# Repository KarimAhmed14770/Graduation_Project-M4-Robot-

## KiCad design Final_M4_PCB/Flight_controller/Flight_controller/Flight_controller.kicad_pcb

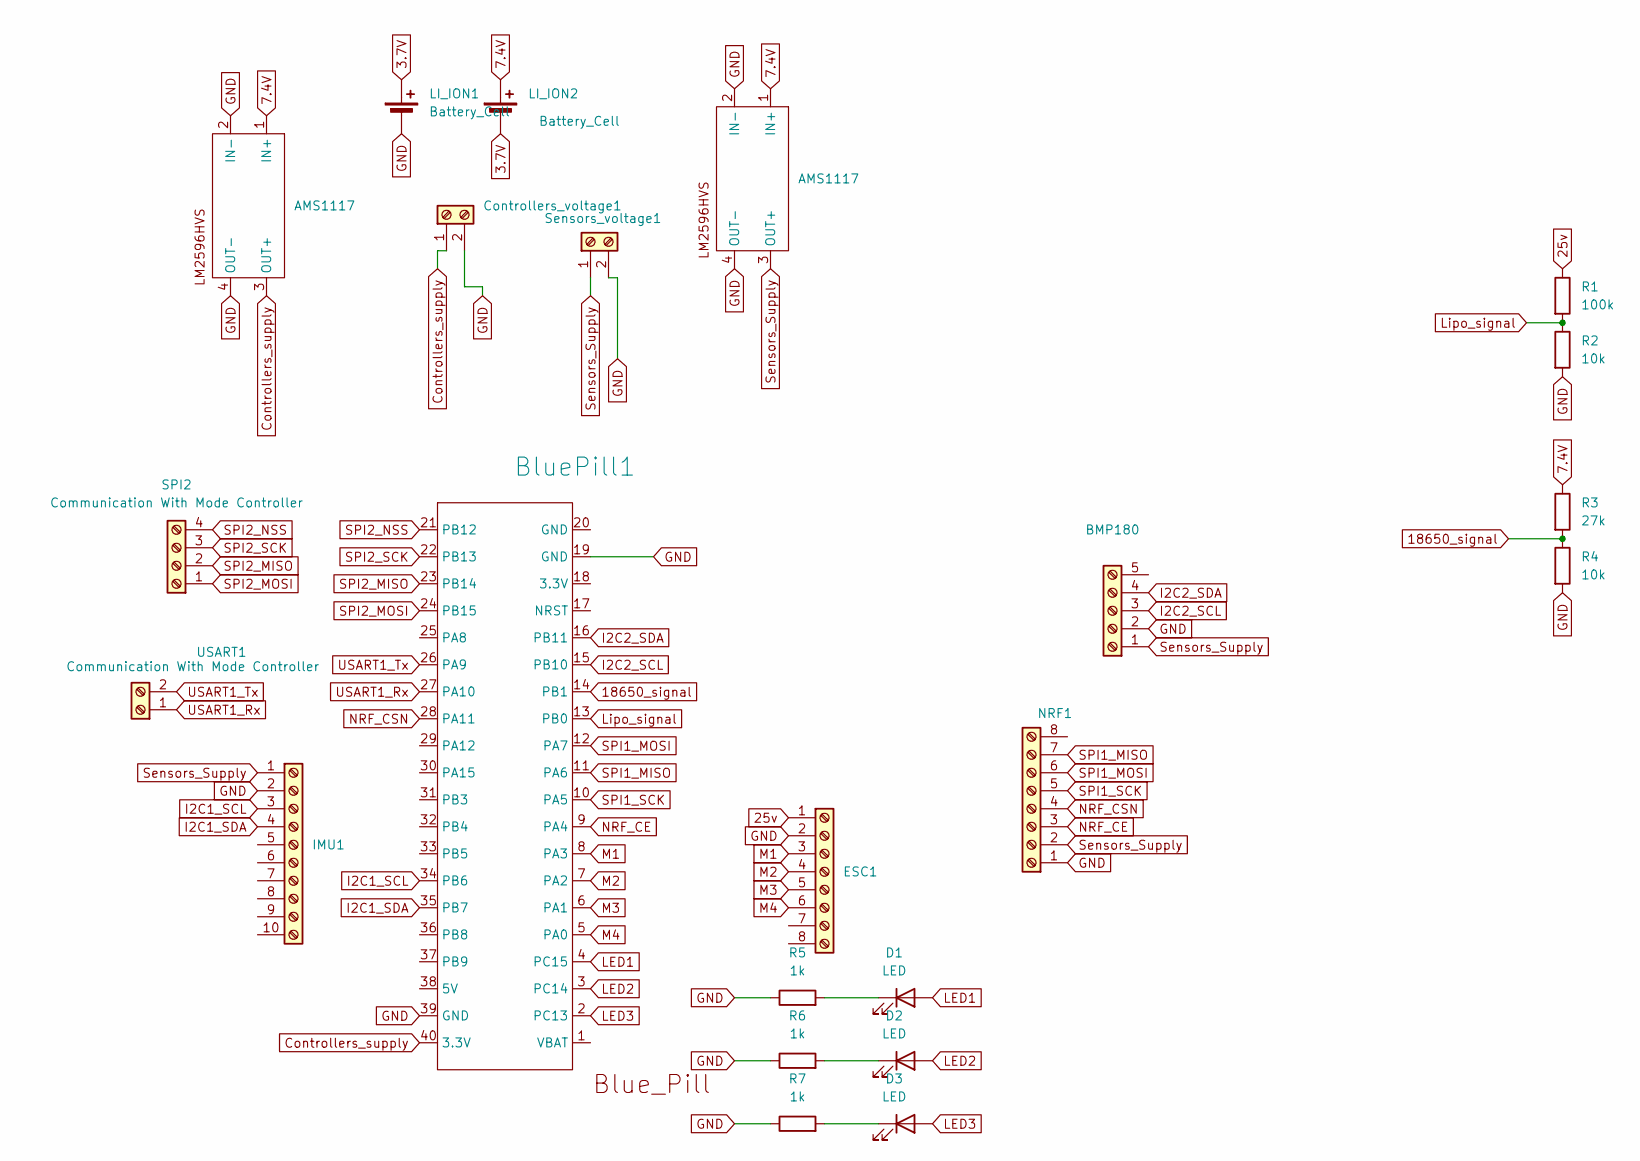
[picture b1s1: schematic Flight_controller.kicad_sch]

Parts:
AMS1117: 3.3v_regulator
BMP180: Screw_Terminal_01x05; BMP180
BluePill1: blue_pill
Controllers_voltage1: Screw_Terminal_01x02; PinHeader_1x02_P2.54mm_Vertical
D1, D2, D3: LED; LED_D3.0mm
ESC1: Screw_Terminal_01x08; ESC
IMU1: Screw_Terminal_01x10; MPU9250
LI_ION1, LI_ION2: Battery_Cell; PinHeader_1x02_P2.54mm_Vertical
NRF1: Screw_Terminal_01x08; NRF24L1
R1: 100k; R_Axial_DIN0204_L3.6mm_D1.6mm_P2.54mm_Vertical
R2, R4: 10k; R_Axial_DIN0204_L3.6mm_D1.6mm_P2.54mm_Vertical
R3: 27k; R_Axial_DIN0204_L3.6mm_D1.6mm_P2.54mm_Vertical
R5, R6, R7: 1k; R_Axial_DIN0204_L3.6mm_D1.6mm_P2.54mm_Vertical
SPI2: Communication With Mode Controller; PinHeader_1x04_P2.54mm_Vertical
Sensors_voltage1: Screw_Terminal_01x02; PinHeader_1x02_P2.54mm_Vertical
USART1: Communication With Mode Controller; PinHeader_1x02_P2.54mm_Vertical

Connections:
3.7V: LI_ION1.1 (+), LI_ION2.2 (-)
7.4V: AMS1117.1 (IN+), LI_ION2.1 (+), R3.1; also elsewhere on the board
25v: ESC1.1, R1.1
18650_signal: BluePill1.14 (PB1), R3.2, R4.1
Controllers_supply: AMS1117.3 (OUT+), BluePill1.40 (3.3V), Controllers_voltage1.1; also elsewhere on the board
GND: AMS1117.2 (IN-), AMS1117.4 (OUT-), BMP180.2, BluePill1.19 (GND), BluePill1.39 (GND), Controllers_voltage1.2, ESC1.2, IMU1.2, LI_ION1.2 (-), NRF1.1, R2.2, R4.2, R5.1, R6.1, R7.1, Sensors_voltage1.2; also elsewhere on the board
I2C1_SCL: BluePill1.34 (PB6), IMU1.3
I2C1_SDA: BluePill1.35 (PB7), IMU1.4
I2C2_SCL: BMP180.3, BluePill1.15 (PB10)
I2C2_SDA: BMP180.4, BluePill1.16 (PB11)
LED1: BluePill1.4 (PC15), D1.2 (A)
LED2: BluePill1.3 (PC14), D2.2 (A)
LED3: BluePill1.2 (PC13), D3.2 (A)
Lipo_signal: BluePill1.13 (PB0), R1.2, R2.1
M1: BluePill1.8 (PA3), ESC1.3
M2: BluePill1.7 (PA2), ESC1.4
M3: BluePill1.6 (PA1), ESC1.5
M4: BluePill1.5 (PA0), ESC1.6
NRF_CE: BluePill1.9 (PA4), NRF1.3
NRF_CSN: BluePill1.28 (PA11), NRF1.4
unnamed: D1.1 (K), R5.2
unnamed: D2.1 (K), R6.2
unnamed: D3.1 (K), R7.2
SPI1_MISO: BluePill1.11 (PA6), NRF1.7
SPI1_MOSI: BluePill1.12 (PA7), NRF1.6
SPI1_SCK: BluePill1.10 (PA5), NRF1.5
SPI2_MISO: BluePill1.23 (PB14), SPI2.2
SPI2_MOSI: BluePill1.24 (PB15), SPI2.1
SPI2_NSS: BluePill1.21 (PB12), SPI2.4
SPI2_SCK: BluePill1.22 (PB13), SPI2.3
Sensors_Supply: AMS1117.3 (OUT+), BMP180.1, IMU1.1, NRF1.2, Sensors_voltage1.1; also elsewhere on the board
USART1_Rx: BluePill1.27 (PA10), USART1.1
USART1_Tx: BluePill1.26 (PA9), USART1.2

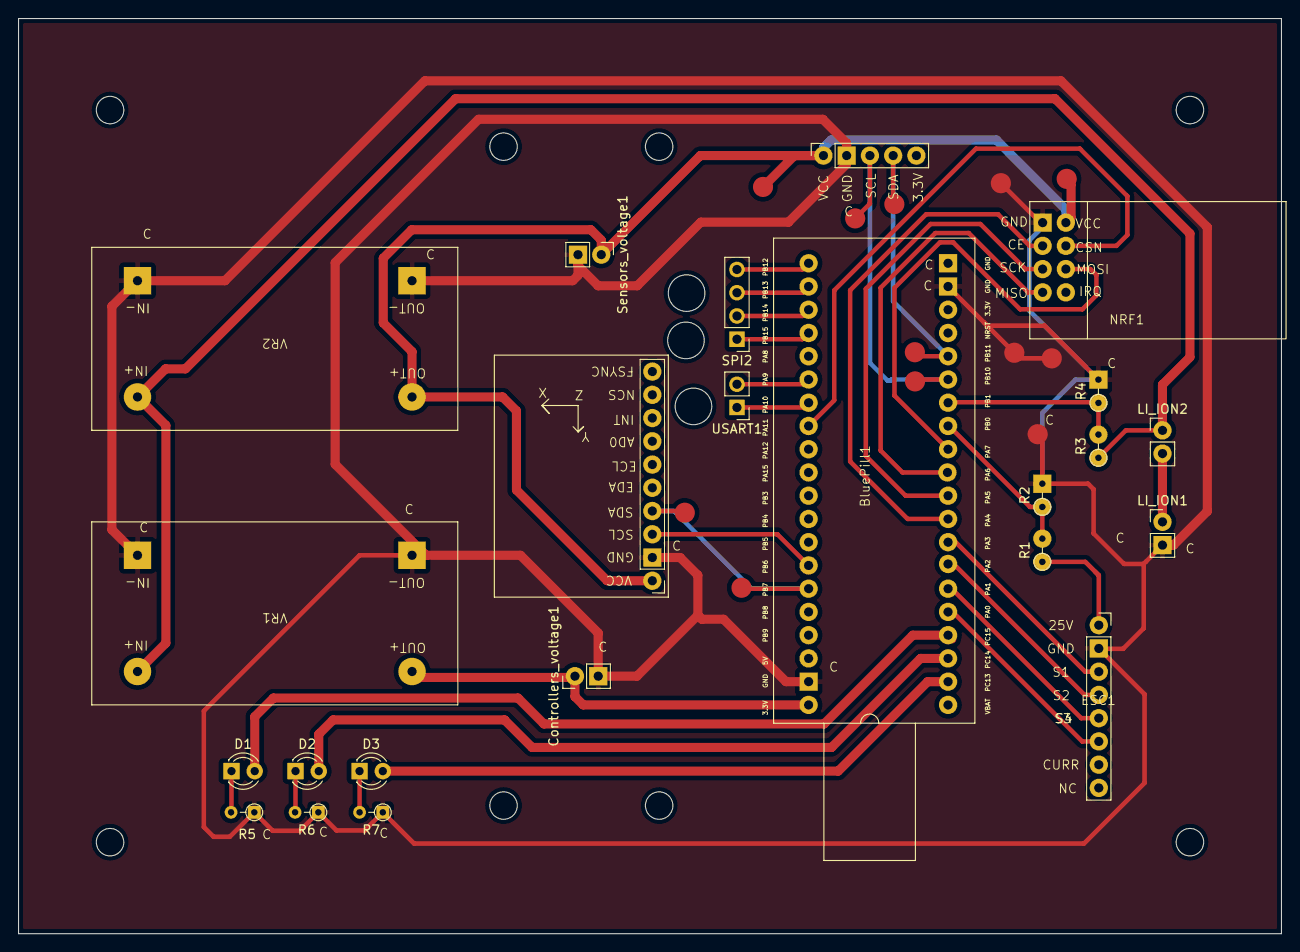
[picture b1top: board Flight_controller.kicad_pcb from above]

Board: 2 copper layers, 138.0 x 100.0 mm, 23 parts (0 on the bottom side), 33 nets.

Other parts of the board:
VR1, VR2: 3.3v_regulator

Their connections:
7.4V: VR1.1 (IN+), VR2.1 (IN+); also elsewhere on the board
Controllers_supply: VR1.3 (OUT+); also elsewhere on the board
GND: VR1.2 (IN-), VR1.4 (OUT-), VR2.2 (IN-), VR2.4 (OUT-); also elsewhere on the board
Sensors_Supply: VR2.3 (OUT+); also elsewhere on the board

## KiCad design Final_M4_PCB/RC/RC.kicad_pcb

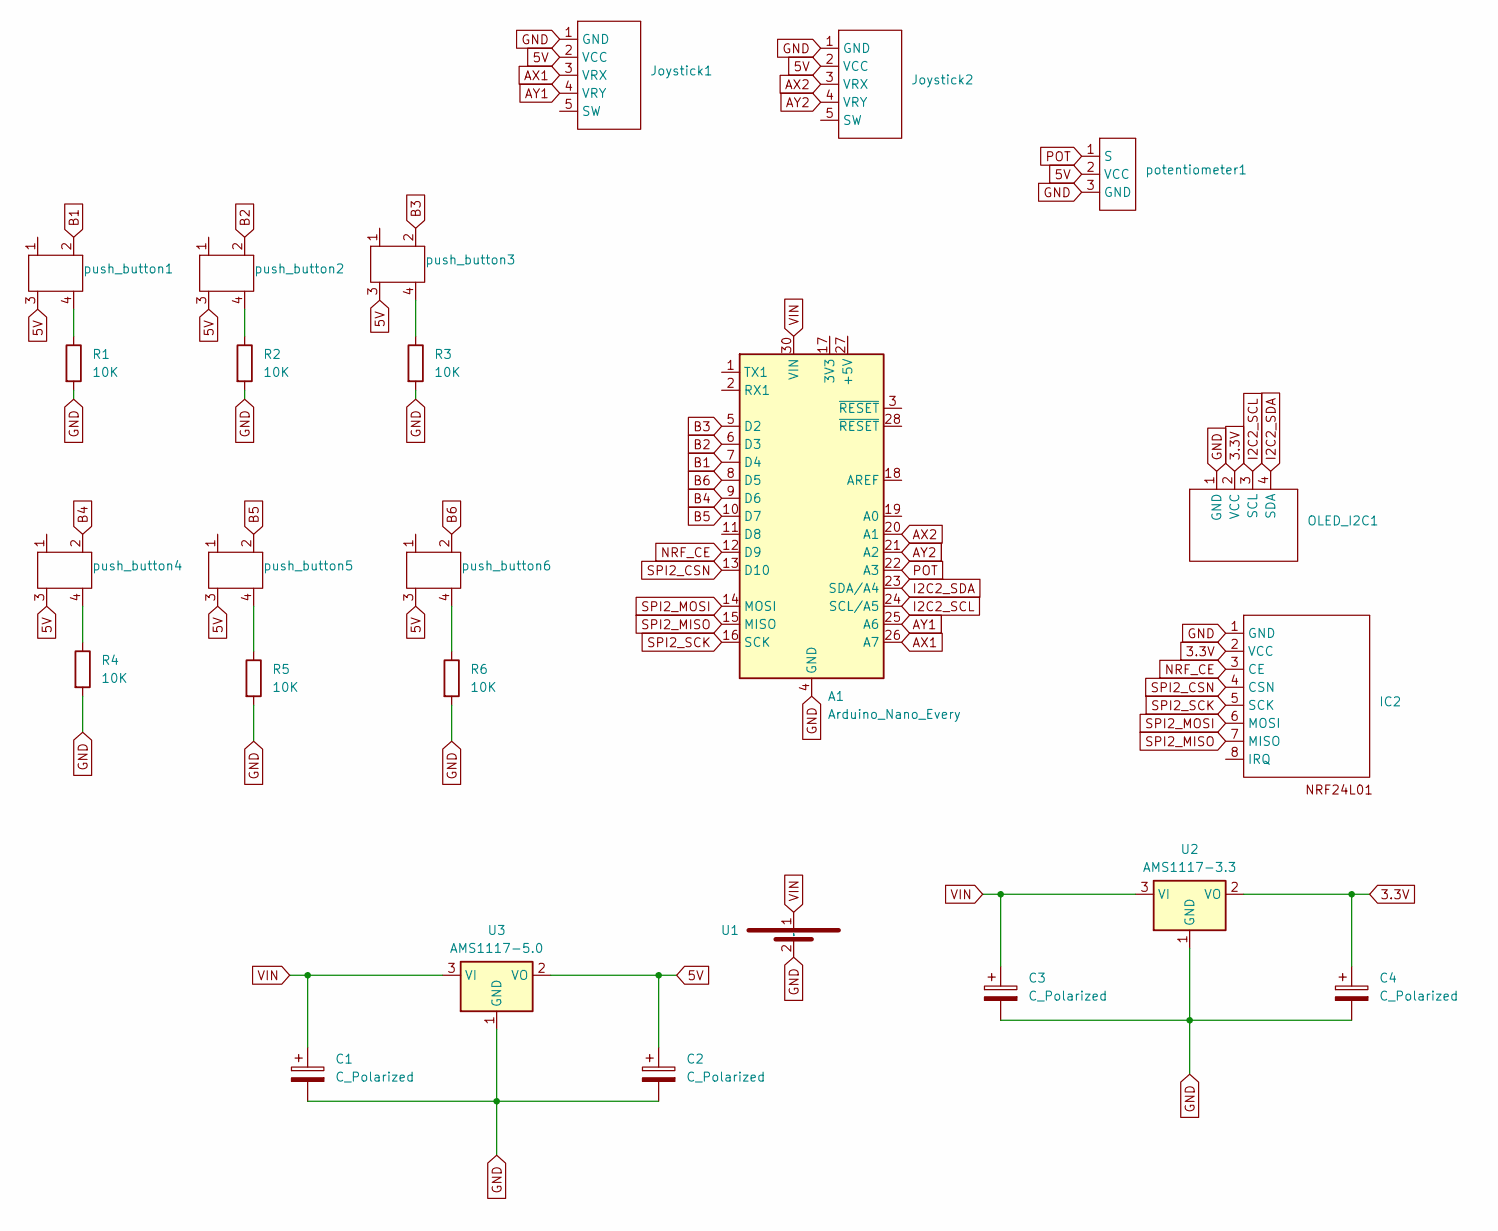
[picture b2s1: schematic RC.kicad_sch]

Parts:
A1: Arduino_Nano_Every; Arduino_Nano
C1, C2, C3, C4: C_Polarized; two_pin_headers2.54
IC2: NRF_ANTENNA
Joystick1, Joystick2: Joystick
OLED_I2C1: OLED
R1, R2, R3, R4, R5, R6: 10K; R_Axial_DIN0204_L3.6mm_D1.6mm_P5.08mm_Horizontal
U1: TerminalBlock_bornier-2_P5.08mm
U2: AMS1117-3.3; SOT-223-3_TabPin2
U3: AMS1117-5.0; SOT-223-3_TabPin2
potentiometer1: POT
push_button1, push_button2, push_button3, push_button4, push_button5, push_button6: Push_Button

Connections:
3.3V: C4.1, IC2.2 (VCC), OLED_I2C1.2 (VCC), U2.2 (VO)
5V: C2.1, Joystick1.2 (VCC), Joystick2.2 (VCC), U3.2 (VO), potentiometer1.2 (VCC), push_button1.3, push_button2.3, push_button3.3, push_button4.3, push_button5.3, push_button6.3
AX1: A1.26 (A7), Joystick1.3 (VRX)
AX2: A1.20 (A1), Joystick2.3 (VRX)
AY1: A1.25 (A6), Joystick1.4 (VRY)
AY2: A1.21 (A2), Joystick2.4 (VRY)
B1: A1.7 (D4), push_button1.2
B2: A1.6 (D3), push_button2.2
B3: A1.5 (D2), push_button3.2
B4: A1.9 (D6), push_button4.2
B5: A1.10 (D7), push_button5.2
B6: A1.8 (D5), push_button6.2
GND: A1.4 (GND), A1.29 (GND), C1.2, C2.2, C3.2, C4.2, IC2.1 (GND), Joystick1.1 (GND), Joystick2.1 (GND), OLED_I2C1.1 (GND), R1.2, R2.2, R3.2, R4.2, R5.2, R6.2, U1.2 (GND), U2.1 (GND), U3.1 (GND), potentiometer1.3 (GND)
I2C2_SCL: A1.24 (SCL/A5), OLED_I2C1.3 (SCL)
I2C2_SDA: A1.23 (SDA/A4), OLED_I2C1.4 (SDA)
NRF_CE: A1.12 (D9), IC2.3 (CE)
unnamed: R1.1, push_button1.4
unnamed: R2.1, push_button2.4
unnamed: R3.1, push_button3.4
unnamed: R4.1, push_button4.4
unnamed: R5.1, push_button5.4
unnamed: R6.1, push_button6.4
POT: A1.22 (A3), potentiometer1.1 (S)
SPI2_CSN: A1.13 (D10), IC2.4 (CSN)
SPI2_MISO: A1.15 (MISO), IC2.7 (MISO)
SPI2_MOSI: A1.14 (MOSI), IC2.6 (MOSI)
SPI2_SCK: A1.16 (SCK), IC2.5 (SCK)
VIN: A1.30 (VIN), C1.1, C3.1, U1.1 (VDD), U2.3 (VI), U3.3 (VI)

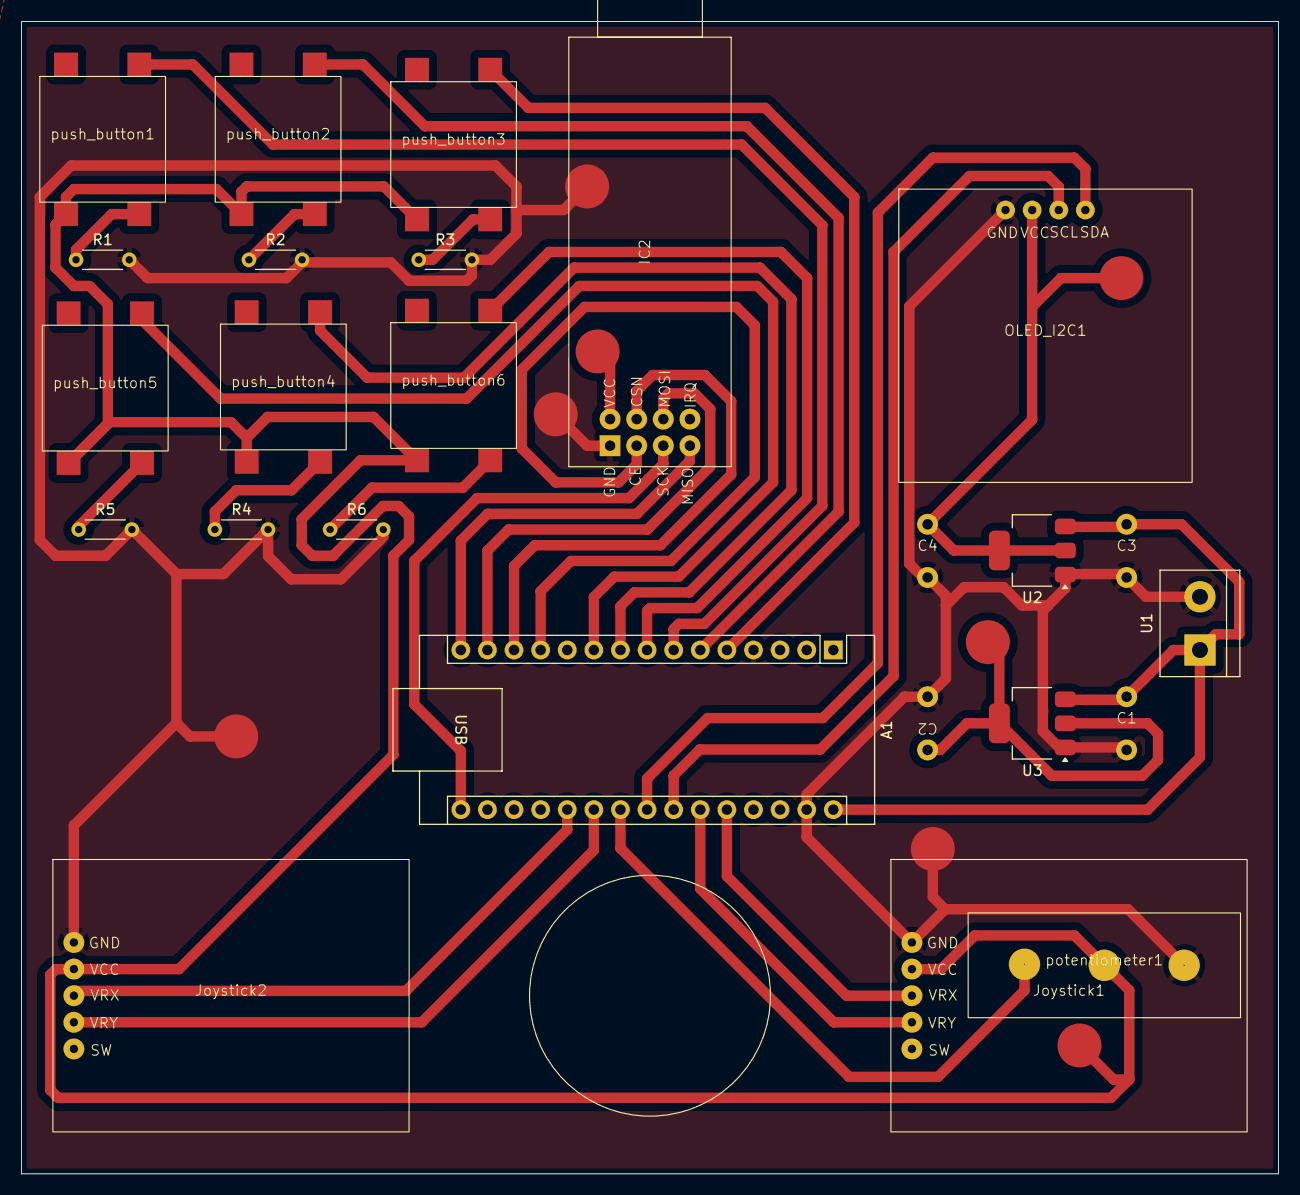
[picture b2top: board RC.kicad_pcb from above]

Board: 2 copper layers, 120.0 x 110.0 mm, 25 parts (0 on the bottom side), 28 nets.

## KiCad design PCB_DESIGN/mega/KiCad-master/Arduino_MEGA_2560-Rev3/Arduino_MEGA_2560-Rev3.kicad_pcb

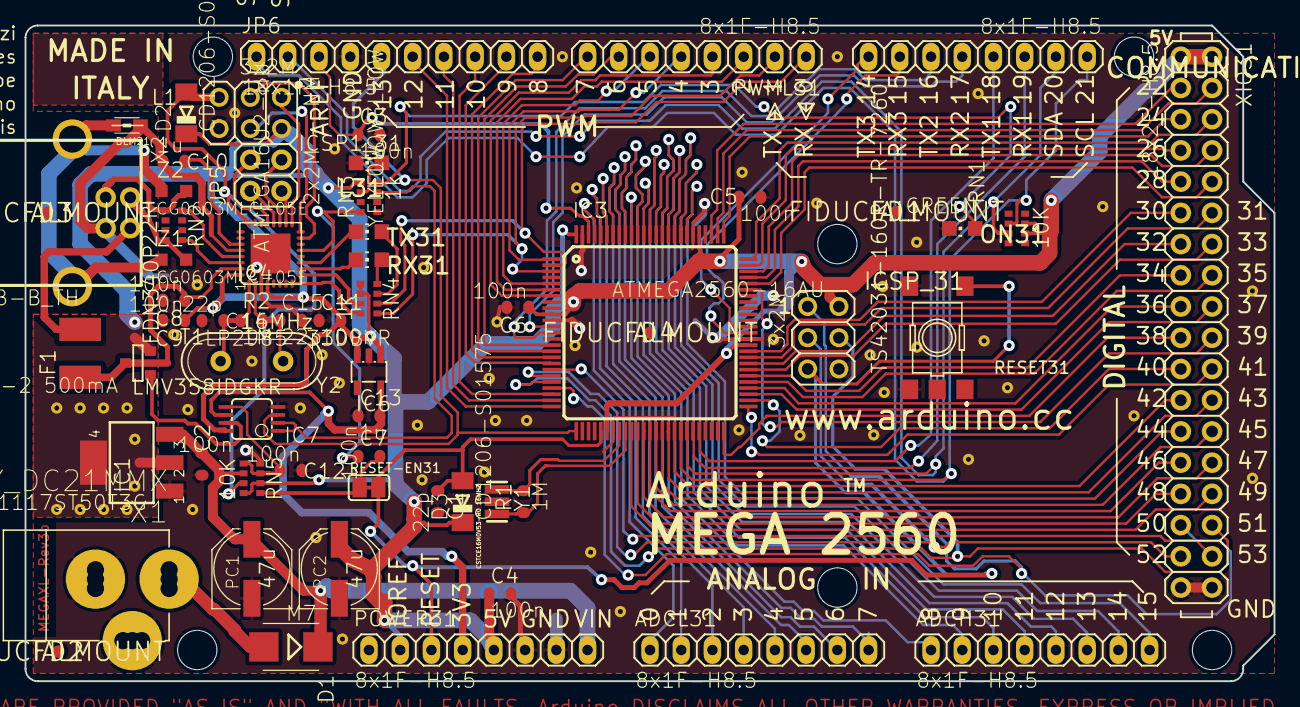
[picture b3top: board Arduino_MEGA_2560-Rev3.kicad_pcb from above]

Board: 2 copper layers, 101.6 x 53.3 mm, 69 parts (1 on the bottom side), 110 nets.

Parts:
@HOLE0, @HOLE1, @HOLE2, @HOLE3, @HOLE4, @HOLE5: (no value)
ADCH31: 8x1F-H8.5; 1X08
ADCL31: 8x1F-H8.5; 1X08
C1, C14, C15: 22p; C0603-ROUND
C2, C3, C4, C5, C6, C7, C8, C9, C11, C12: 100n; C0603-ROUND
C10, C13: 1u; C0603-ROUND
COMMUNICATION31: 8x1F-H8.5; 1X08
D1: M7; SMB
D2, D3: CD1206-S01575; MINIMELF
F1: MF-MSMF050-2 500mA; L1812
FD1, FD2, FD3, FD4: FIDUCIALMOUNT; FIDUCIA-MOUNT
GROUND31: SJ
IC1: NCP1117ST50T3G; SOT223
IC3: ATMEGA2560-16AU; TQFP100
IC4: ATMEGA16U2-MU; MLF32
IC6: LP2985-33DBVR; SOT23-DBV
IC7: LMV358IDGKR; MSOP08
ICSP1_31: 3x2M; 2X03
ICSP_31: 3x2M; 2X03
JP5: 2x2M - NM; 2X02
JP6: 10x1F-H8.5; 1X10
L1: BLM21; 0805
L31: YELLOW; CHIP-LED0805
ON31: GREEN; CHIP-LED0805
PC1, PC2: 47u; PANASONIC_D
POWER31: 8x1F-H8.5; 1X08
PWML31: 8x1F-H8.5; 1X08
R1, R2: 1M; R0603-ROUND
RESET31: TS42031-160R-TR-7260; TS42
RESET-EN31: SJ
RN1, RN5: 10K; CAT16
RN2: 22R; CAY16
RN3, RN4: 1k; CAY16
RX31: YELLOW; CHIP-LED0805
T1: FDN340P; SOT-23
TX31: YELLOW; CHIP-LED0805
U$1: DISCLAIMER
X1: POWERSUPPLY_DC21MMX; POWERSUPPLY_DC-21MM
X2: USB-B_TH; PN61729
XIO31: 18x2F-H8.5; 2X18
Y1: CSTCE16M0V53-R0 16MHZ; RESONATOR
Y2: 16MHz; QS
Z1, Z2: CG0603MLC-05E; CT%2fCN0603

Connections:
+3V3: C13.2, IC6.5, IC7.6, POWER31.4
+5V: C4.1, C5.1, C6.1, C9.1, C11.2, D2.C, D3.C, IC1.2, IC1.4, IC3.10, IC3.31, IC3.61, IC3.80, IC3.100, IC4.4, IC4.32, IC6.1, IC6.3, IC7.8, ICSP1_31.2, ICSP_31.2, PC2.+, POWER31.2, POWER31.5, RN1.6, RN1.7, RN3.1, RN4.5, RN4.6, RN5.2, RN5.8, T1.2, XIO31.1, XIO31.2
/8PB4: IC4.18, JP5.1
/8PB5: IC4.19, JP5.3
/8PB6: IC4.20, JP5.2
/8PB7: IC4.21, JP5.4
/ADC0: ADCL31.1, IC3.97
/ADC1: ADCL31.2, IC3.96
/ADC2: ADCL31.3, IC3.95
/ADC3: ADCL31.4, IC3.94
/ADC4: ADCL31.5, IC3.93
/ADC5: ADCL31.6, IC3.92
/ADC6: ADCL31.7, IC3.91
/ADC7: ADCL31.8, IC3.90
/ADC8: ADCH31.1, IC3.89
/ADC9: ADCH31.2, IC3.88
/ADC10: ADCH31.3, IC3.87
/ADC11: ADCH31.4, IC3.86
/ADC12: ADCH31.5, IC3.85
/ADC13: ADCH31.6, IC3.84
/ADC14: ADCH31.7, IC3.83
/ADC15: ADCH31.8, IC3.82
/AREF: C3.1, IC3.98, JP6.3
/CMP: C12.2, IC7.5, RN5.3, RN5.5
/D+: RN2.5, X2.3, Z2.2
/D-: RN2.8, X2.2, Z1.2
/DTR: C7.1, IC4.13, RN3.4
/GATE_CMD: IC7.7, T1.3
/L13: IC7.1, IC7.2, RN3.7
/M8RXD: IC4.9, RN4.7
/M8TXD: IC4.8, RN4.8
/MISO2: IC4.17, ICSP1_31.1
/MOSI2: IC4.16, ICSP1_31.4
/N$2: L31.A, RN3.2
/N$3: ON31.A, RN3.8
/N$54: RN4.4, RX31.A
/N$55: RN4.3, TX31.A
/PA0: IC3.78, XIO31.3
/PA1: IC3.77, XIO31.4
/PA2: IC3.76, XIO31.5
/PA3: IC3.75, XIO31.6
/PA4: IC3.74, XIO31.7
/PA5: IC3.73, XIO31.8
/PA6: IC3.72, XIO31.9
/PA7: IC3.71, XIO31.10
/PB0: IC3.19, XIO31.34
/PB1: IC3.20, ICSP_31.3, XIO31.33
/PB2: IC3.21, ICSP_31.4, XIO31.32
/PB3: IC3.22, ICSP_31.1, XIO31.31
/PB4: IC3.23, JP6.8
/PB5: IC3.24, JP6.7
/PB6: IC3.25, JP6.6
/PB7: IC3.26, IC7.3, JP6.5
/PC0: IC3.53, XIO31.18
/PC1: IC3.54, XIO31.17
/PC2: IC3.55, XIO31.16
/PC3: IC3.56, XIO31.15
/PC4: IC3.57, XIO31.14
/PC5: IC3.58, XIO31.13
/PC6: IC3.59, XIO31.12
/PC7: IC3.60, XIO31.11
/PD7: IC3.50, XIO31.19
/PE0: IC3.2, PWML31.1, RN4.2
/PE1: IC3.3, PWML31.2, RN4.1
/PE3: IC3.5, PWML31.6
/PE4: IC3.6, PWML31.3
/PE5: IC3.7, PWML31.4
/PG0: IC3.51, XIO31.22
/PG1: IC3.52, XIO31.21
/PG2: IC3.70, XIO31.20
/PG5: IC3.1, PWML31.5
/PH3: IC3.15, PWML31.7
/PH4: IC3.16, PWML31.8
/PH5: IC3.17, JP6.10
/PH6: IC3.18, JP6.9
/PL0: IC3.35, XIO31.30
/PL1: IC3.36, XIO31.29
/PL2: IC3.37, XIO31.28
/PL3: IC3.38, XIO31.27
/PL4: IC3.39, XIO31.26
/PL5: IC3.40, XIO31.25
/PL6: IC3.41, XIO31.24
/PL7: IC3.42, XIO31.23
/PWRIN: D1.A, X1.2
/RD+: IC4.29, RN2.4
/RD-: IC4.30, RN2.1
/RESET: C1.1, C7.2, D3.A, IC3.30, ICSP_31.5, POWER31.3, RESET31.3, RESET31.4, RESET-EN31.1, RESET-EN31.2, RN5.1
/RESET2: D2.A, IC4.24, ICSP1_31.5, RN5.7
/RXD1: COMMUNICATION31.3, IC3.45
/RXD2: COMMUNICATION31.5, IC3.12
/RXD3: COMMUNICATION31.7, IC3.63
/RXL: IC4.10, RX31.C
/SCK2: IC4.15, ICSP1_31.3
/SCL: COMMUNICATION31.1, IC3.43, JP6.1, RN1.2
/SDA: COMMUNICATION31.2, IC3.44, JP6.2, RN1.3
/TXD1: COMMUNICATION31.4, IC3.46
/TXD2: COMMUNICATION31.6, IC3.13
/TXD3: COMMUNICATION31.8, IC3.64
/TXL: IC4.11, TX31.C
/UGND: C10.2, GROUND31.1, IC4.28, L1.1, X2.4
/USBVCC: C8.1, F1.1, IC4.31, T1.1
/USHIELD: L1.2, X2.P$1, X2.P$2, Z1.1, Z2.1
/VIN: C2.1, D1.C, IC1.3, PC1.+, POWER31.8, RN5.6
/VUCAP: C10.1, IC4.27
/XT1: C14.1, IC4.1, R2.1, Y2.2
/XT2: C15.1, IC4.2, R2.2, Y2.1
/XTAL1: IC3.34, R1.1, Y1.3
/XTAL2: IC3.33, R1.2, Y1.1
/XVCC: F1.2, X2.1
GND: C1.2, C2.2, C3.2, C4.2, C5.2, C6.2, C8.2, C9.2, C11.1, C12.1, C13.1, C14.2, C15.2, GROUND31.2, IC1.1, IC3.11, IC3.32, IC3.62, IC3.81, IC3.99, IC4.3, IC4.33, IC6.2, IC7.4, ICSP1_31.6, ICSP_31.6, JP6.4, L31.C, ON31.C, PC1.-, PC2.-, POWER31.6, POWER31.7, RESET31.1, RESET31.2, RN3.5, RN5.4, X1.1, X1.3, XIO31.35, XIO31.36, Y1.2
